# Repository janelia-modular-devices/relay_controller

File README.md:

# relay_controller

Authors:

    Peter Polidoro <polidorop@janelia.hhmi.org>

License:

    BSD

## More Detailed Help on Installation and Usage

[modular-devices](https://github.com/janelia-modular-devices/modular-devices)

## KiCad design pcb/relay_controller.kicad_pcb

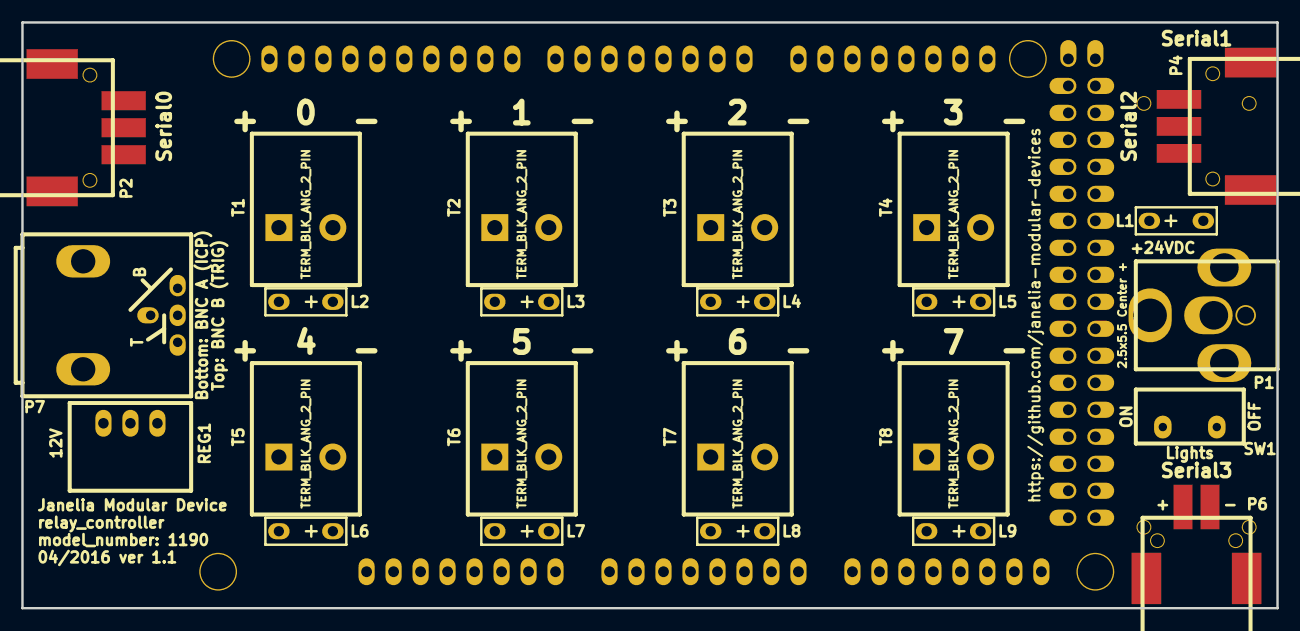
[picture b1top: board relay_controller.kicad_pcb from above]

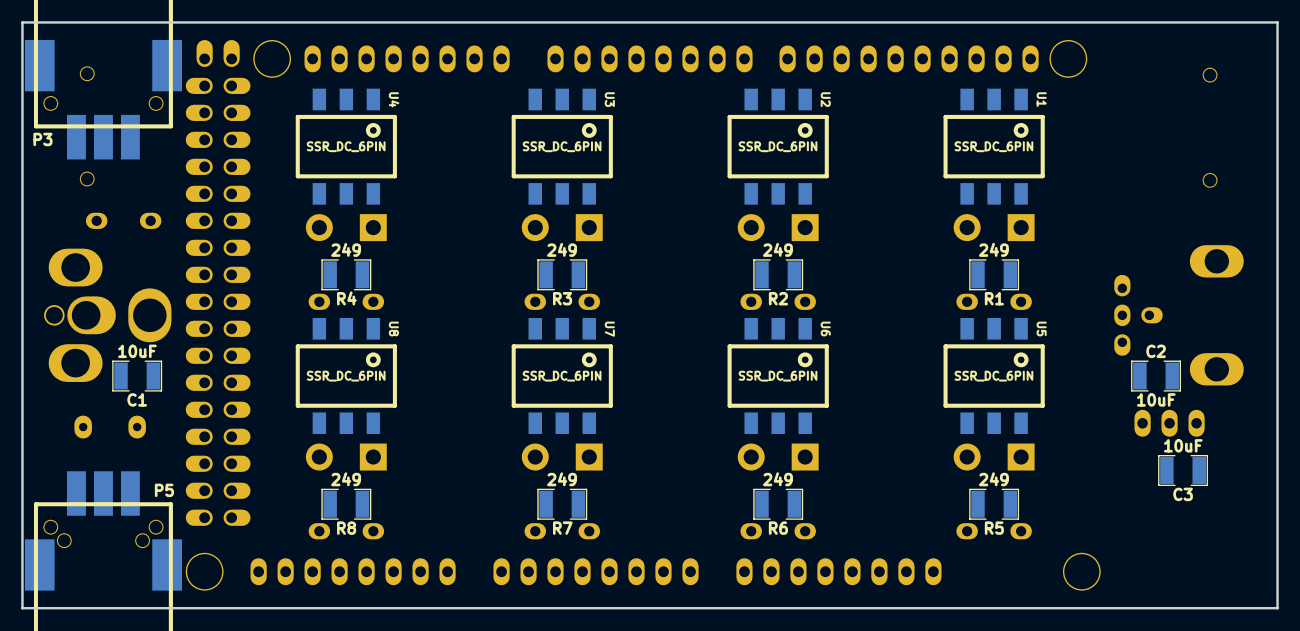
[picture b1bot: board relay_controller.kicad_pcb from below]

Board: 2 copper layers, 118.1 x 55.1 mm, 46 parts (21 on the bottom side), 46 nets, no tracks yet.

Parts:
ARDUINO1: ARDUINO_MEGA; ARDUINO_MEGA_SHIELD
C1, C2, C3: 10uF; SM1210
L1: LED_24V; LED_555-3XXX
L2, L3, L4, L5, L6, L7, L8, L9: LED_5V_GRN; LED_555-3XXX
P1: PWR_JACK_2.5x5.5; DCJACK_2PIN_HIGHCURRENT
P2, P3, P4, P5: HEADER_01X03_SMD_RA; Header_3_Pin_SMD_RA
P6: HEADER_01X02_SMD_RA; Header_2_Pin_SMD_RA
P7: BNC_DOUBLE_RA; BNC_DOUBLE
R1, R2, R3, R4, R5, R6, R7, R8: 249; SM1210
REG1: CONV_DC_DC_12V_1A; DC_DC_CONV_R78C
SW1: SPST_SLIDE_AS
T1, T2, T3, T4, T5, T6, T7, T8: TERM_BLK_ANG_2_PIN
U1, U2, U3, U4, U5, U6, U7, U8: SSR_DC_6PIN; ASSR-1611

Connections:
/BNC_A: ARDUINO1.48, P7.1
/BNC_B: ARDUINO1.3, P7.3
/LED_GND: L1.2, L2.2, L3.2, L4.2, L5.2, L6.2, L7.2, L8.2, L9.2, SW1.3
/OUT_0+: T1.1, U1.4, U1.6
/OUT_0-: T1.2, U1.5
/OUT_1+: T2.1, U2.4, U2.6
/OUT_1-: T2.2, U2.5
/OUT_2+: T3.1, U3.4, U3.6
/OUT_2-: T3.2, U3.5
/OUT_3+: T4.1, U4.4, U4.6
/OUT_3-: T4.2, U4.5
/OUT_4+: T5.1, U5.4, U5.6
/OUT_4-: T5.2, U5.5
/OUT_5+: T6.1, U6.4, U6.6
/OUT_5-: T6.2, U6.5
/OUT_6+: T7.1, U7.4, U7.6
/OUT_6-: T7.2, U7.5
/OUT_7+: T8.1, U8.4, U8.6
/OUT_7-: T8.2, U8.5
/RELAY_0: ARDUINO1.8, L2.1, R1.2
/RELAY_1: ARDUINO1.9, L3.1, R2.2
/RELAY_2: ARDUINO1.10, L4.1, R3.2
/RELAY_3: ARDUINO1.11, L5.1, R4.2
/RELAY_4: ARDUINO1.12, L6.1, R5.2
/RELAY_5: ARDUINO1.44, L7.1, R6.2
/RELAY_6: ARDUINO1.45, L8.1, R7.2
/RELAY_7: ARDUINO1.46, L9.1, R8.2
/RX0: ARDUINO1.0, P2.1
/RX1: ARDUINO1.19, P3.1
/RX2: ARDUINO1.17, P4.1
/RX3: ARDUINO1.15, P5.1
/TX0: ARDUINO1.1, P2.3
/TX1: ARDUINO1.18, P3.3
/TX2: ARDUINO1.16, P4.3
/TX3: ARDUINO1.14, P5.3
/V_IN: ARDUINO1.V_IN, C3.1, REG1.3
GND: ARDUINO1.GND1, ARDUINO1.GND2, C1.2, C2.2, C3.2, P1.2, P2.2, P3.2, P4.2, P5.2, P6.1, P7.2, P7.4, REG1.2, SW1.1, U1.2, U2.2, U3.2, U4.2, U5.2, U6.2, U7.2, U8.2
unnamed: R1.1, U1.1
unnamed: R2.1, U2.1
unnamed: R3.1, U3.1
unnamed: R4.1, U4.1
unnamed: R5.1, U5.1
unnamed: R6.1, U6.1
unnamed: R7.1, U7.1
unnamed: R8.1, U8.1
VAA: C1.1, C2.1, L1.1, P1.1, P6.2, REG1.1

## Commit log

2016-04-04 Initial commit.
2016-04-04 Progress towards pcb1.0.
2016-04-05 More progress towards pcb1.0.
2016-04-06 pcb1.0 completed.
2016-04-08 Switched LED_PWR to LED_GND.
2016-04-25 Made changes to 1.1, must complete before manufacturing boards.
2016-08-08 Removed traces.
2016-09-19 Updated spaces around pointers and references.
2016-09-21 pcb -> hardware.
2017-01-04 Removed hardware.
2017-01-04 Added hardware/relay_controller_5x3.
2017-02-02 Updated hardware/relay_controller_5x3.
2017-03-29 Updated documentation.
2018-04-12 Updated submodules.
2018-04-12 *.md -> *.org.
2018-05-18 Submodule update.
2018-08-12 polidorop@janelia.hhmi.org -> peterpolidoro@gmail.com
2018-08-27 Combined software and hardware licenses.
2021-09-17 Update email address
